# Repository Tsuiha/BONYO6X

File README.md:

# BONYO6X

　BONYO6Xは60%キーボードの汎用ケース、所謂Poker, GH60, DZ60等に対応したケースと互換性のあるPCBです。
 
　他人でも初見で使える, 自分でも不満なく使える, ことをコンセプトとしています。基本的なANSIは崩さずにカスタマイズ性も確保した構成を目指した、特化型でなく器用貧乏型のキーボードです。
 
　使用用途は実務からラフな普段使いまで, 一台で可もなく不可もなく, 満遍なくこなすことを想定しています。

　リポジトリに設計データが公開されています。 自由にしてください。

　[noteでも紹介しています](https://note.com/tsuiha/m/m13bdadaac60e)

## キー配置

　ANSIをベースに私の趣味を加え以下のようにカスタムしたものになります。

・2U Shift Layout  
　Row StaggeredよりもColumn StaggeredやOrtholinearが好きなこともあり、オフセット量の揃った2U Shiftの方が好みです。

・1.5U, 2U, 1.5U Thumb Cluster  
　2U スペースキーの左右に1.5U Modキーを配置し、レイヤー移動を前提とした配列としています。

・Arrow Keys  
　Arrow KeysがTop Layerにあると痒い時に手が届きます。DZ60系の詰めた配列ではなく、1.75U Shiftを端に、Arrow Keysはその内側に配置しています。

・Tactile Switch  
　キーボード右下にタクトスイッチを搭載可能です。マイクミュート, スクリーンショット, リプレイの保存 等、キースイッチと独立したFunctionキーとして使用できます。

画像はkeyboard-layout-editor.comにて作成しました。

## LED
　LEDが2個搭載可能です。デフォルトでは現在のレイヤーに対応して発光色が変化します。
　発光強度や色、光らせ方はファームウェアを改変し変更することができます。

## タクタイルスイッチ
　タクタイルスイッチが1個搭載可能です。ケース高に応じて高さのあったスイッチを使用してください。フローティングデザインのケースでは7mmのものを、通常デザインのケースでは11mmのものを画像では使用しています。

# 組み立て

## PCB & Switch Plate 
　誰かが製造したものを入手するか、公開されている設計データから自身で製造ください。JLCPCBを使用する際は発注データが公開されています。

## LED SK6812MINI-E x2
　オプションでLEDを取り付けることができます。

## Tactile Switch x1
　オプションでタクトスイッチを取り付けることができます。6x6mmサイズの2pinまたは4pinのものを使用することができます。

## qmk-vial
　ファームウェアにはqmk-vialを使用しています。

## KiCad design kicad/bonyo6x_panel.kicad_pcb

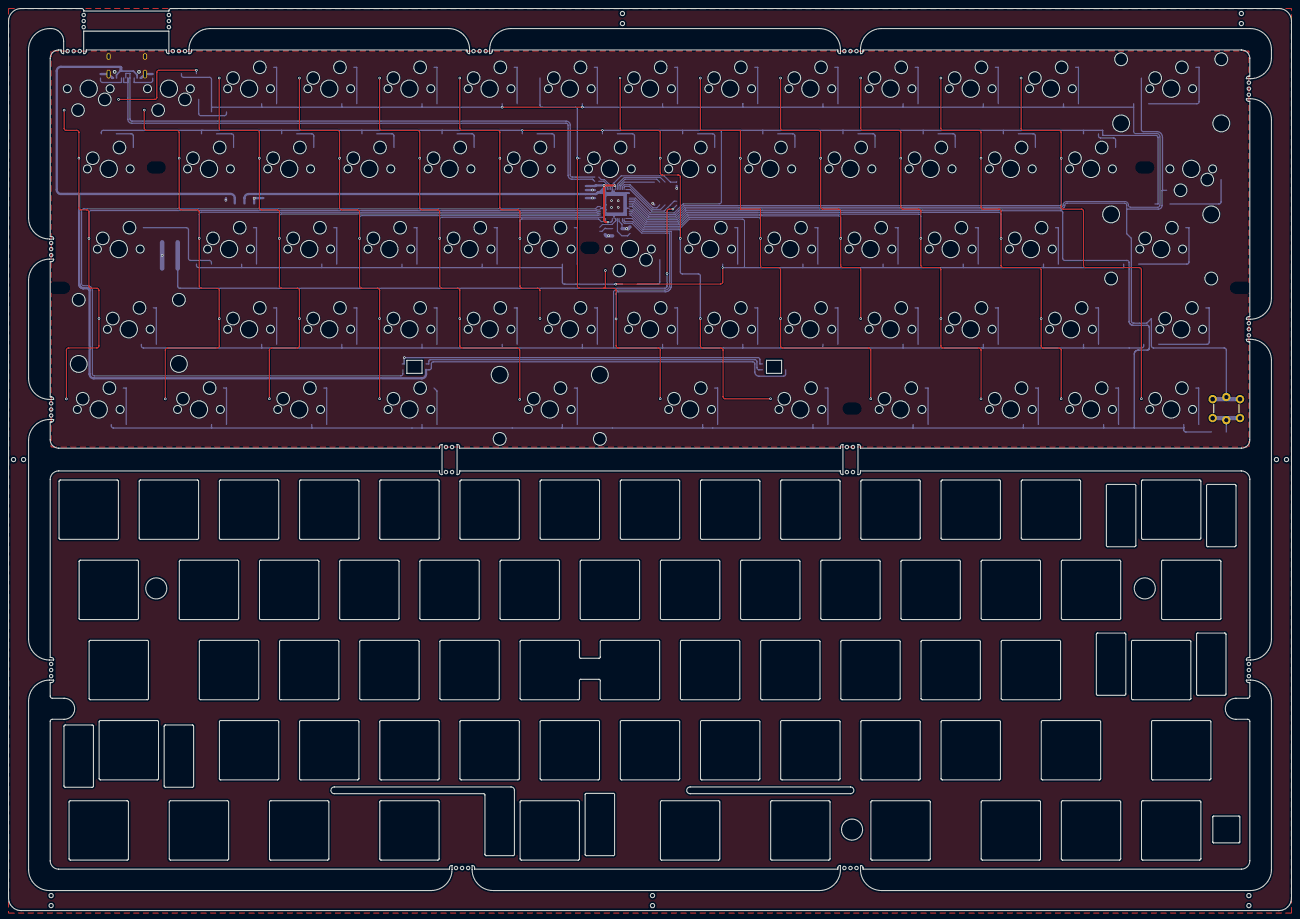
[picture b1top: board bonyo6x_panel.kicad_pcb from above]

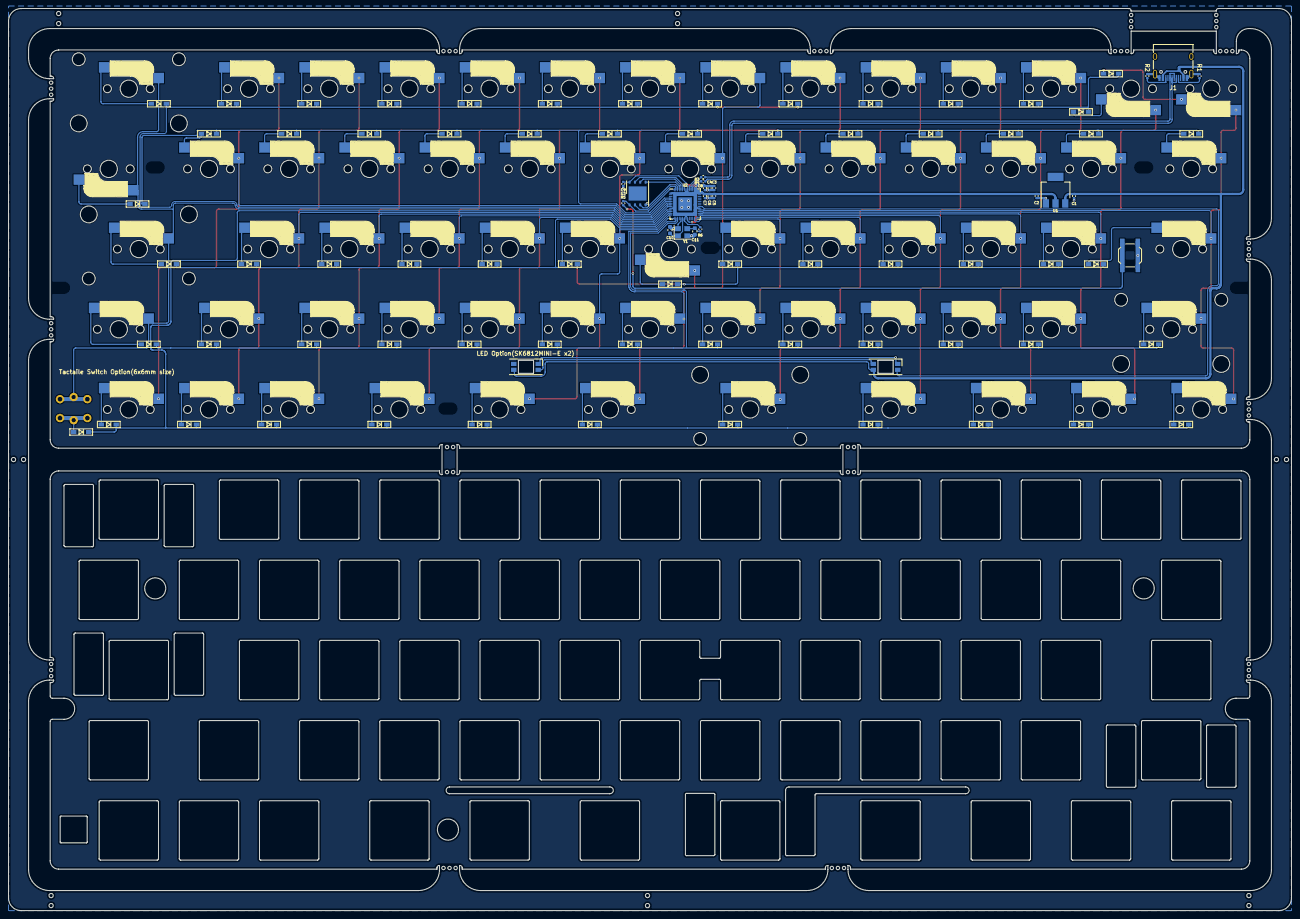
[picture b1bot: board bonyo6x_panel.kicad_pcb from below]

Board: 2 copper layers, 304.7 x 214.2 mm, 220 parts (25 on the bottom side), 107 nets.

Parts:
C1, C2: 10u; C_0402_1005Metric
C3, C4, C5, C6, C9: 100n; C_0402_1005Metric
C7, C8: 1u; C_0402_1005Metric
C10, C11: 30p; C_0603_1608Metric
D1, D2, D3, D4, D5, D6, D7, D8, D9, D10, D11, D12, D13, D14, D15, D16, D17, D18, D19, D20, D21, D22, D23, D24, D25, D26, D27, D28, D29, D30, D31, D32, D33, D34, D35, D36, D37, D38, D39, D40, D41, D42, D43, D44, D45, D46, D47, D48, D49, D50, D51, D52, D53, D54, D55, D56, D57, D58, D59, D60, D61, D62, D63, D64, D65, D66: D; Diode_SMD_noname
J1: USB_C_Receptacle; USB_C_Receptacle_HRO_TYPE-C-31-M-12
LED1, LED2: YS-SK6812MINI-E
R1, R2: 5.1k; C_0402_1005Metric
R3, R4: 27; C_0402_1005Metric
R5, R6: 1k; C_0402_1005Metric
SW1, SW2#2, SW3, SW4#2, SW5, SW6, SW7#2, SW8#2, SW9#2, SW10, SW11#2, SW12, SW13#2, SW16, SW17, SW18#2, SW19, SW20, SW21#2, SW22#2, SW23, SW24, SW25, SW26, SW27, SW30, SW31, SW32, SW33#2, SW34, SW35, SW36, SW37#2, SW38#2, SW39, SW40#2, SW43#2, SW44, SW45#2, SW46, SW47, SW48#2, SW49, SW50#2, SW51#2, SW52#2, SW53, SW63, SW64#2, SW65: SW_PUSH; CherryMX_Hotswap
SW1#2, SW2, SW3#2, SW4, SW5#2, SW6#2, SW7, SW8, SW9, SW10#2, SW11, SW12#2, SW13, SW16#2, SW17#2, SW18, SW19#2, SW20#2, SW21, SW22, SW23#2, SW24#2, SW25#2, SW26#2, SW27#2, SW30#2, SW31#2, SW32#2, SW33, SW36#2, SW37, SW38, SW39#2, SW40, SW43, SW44#2, SW45, SW46#2, SW47#2, SW48, SW49#2, SW50, SW51, SW52, SW53#2, SW63#2, SW64, SW65#2: SW_PUSH; SW_Hole_1u
SW14: SW_PUSH_2; SW_Hole_2u
SW14#2: SW_PUSH_2; CherryMX_Hotswap_2u
SW15, SW28, SW58#2, SW60, SW60#3: SW_PUSH_15; SW_Hole_1u
SW15#2, SW28#2, SW58, SW60#2: SW_PUSH_15; CherryMX_Hotswap_1.5u
SW29, SW54#2: SW_PUSH_175; CherryMX_Hotswap_1.75u
SW29#2, SW54: SW_PUSH_175; SW_Hole_1u
SW41: SW_PUSH_225; CherryMX_Hotswap_2u_r
SW41#2, SW42: SW_PUSH_225; SW_Hole_2u
SW42#2: SW_PUSH_225; CherryMX_Hotswap_2u
SW55, SW56#2, SW57, SW61, SW62#2: SW_PUSH_125; CherryMX_Hotswap_1.25u
SW55#2, SW56, SW57#2, SW61#2, SW62: SW_PUSH_125; SW_Hole_1u
SW59: SW_PUSH_2; CherryMX_Hotswap_2u_r
SW_boot1: SW_BOOT; SW_SPST_SKQG_WithStem
SW_tact1: SW_PUSH; tactileforkh60
U1: AMS1117-3.3; SOT-223
U2: RP2040; QFN-56-1EP_7x7mm_P0.4mm_EP3.2x3.2mm
U3: W25Q128JVS; WSON-8-1EP_6x5mm_P1.27mm_EP3.4x4.3mm
Y1: Crystal_GND24; Crystal_SMD_3225-4Pin_3.2x2.5mm

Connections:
+1V1: C3.1, C4.1, C8.1, U2.23 (DVDD), U2.45 (VREG_VOUT), U2.50 (DVDD)
+3V3: C2.1, C5.1, C6.1, C7.1, C9.1, U1.2 (VO), U2.1 (IOVDD), U2.10 (IOVDD), U2.22 (IOVDD), U2.33 (IOVDD), U2.42 (IOVDD), U2.43 (ADC_AVDD), U2.44 (VREG_IN), U2.48 (USB_VDD), U2.49 (IOVDD), U3.8 (VCC)
+5V: C1.1, J1.A4 (VBUS), J1.A9 (VBUS), J1.B4 (VBUS), J1.B9 (VBUS), LED1.1 (VDD), LED2.1 (VDD), U1.3 (VI)
/QSPI_SCLK: U2.52 (QSPI_SCLK), U3.6 (CLK)
/QSPI_SD0: U2.53 (QSPI_SD0), U3.5 (DI(IO0))
/QSPI_SD1: U2.55 (QSPI_SD1), U3.2 (DO(IO1))
/QSPI_SD2: U2.54 (QSPI_SD2), U3.3 (IO2)
/QSPI_SD3: U2.51 (QSPI_SD3), U3.7 (IO3)
/QSPI_SS: R5.1, U2.56 (QSPI_SS), U3.1 (~CS)
/USB_D+: J1.A6 (D+), J1.B6 (D+), R3.2
/USB_D-: J1.A7 (D-), J1.B7 (D-), R4.2
/XIN: C10.2, U2.20 (XIN), Y1.1
/XOUT: R6.1, U2.21 (XOUT)
/~USB_BOOT: R5.2, SW_boot1.1
GND: C1.2, C2.2, C3.2, C4.2, C5.2, C6.2, C7.2, C8.2, C9.2, C10.1, C11.2, J1.A1 (GND), J1.A12 (GND), J1.B1 (GND), J1.B12 (GND), J1.S1 (SHIELD), LED1.3 (VSS), LED2.3 (VSS), R1.1, R2.1, SW_boot1.2, U1.1 (GND), U2.19 (TESTEN), U2.57 (GND), U3.4 (GND), Y1.2, Y1.4
LED: LED1.4 (DIN), U2.34 (GPIO22)
unnamed: C11.1, R6.2, Y1.3
unnamed: D1.2 (A), SW1.1
unnamed: D2.2 (A), SW2#2.1
unnamed: D3.2 (A), SW3.2
unnamed: D4.2 (A), SW4#2.2
unnamed: D5.2 (A), SW5.2
unnamed: D6.2 (A), SW6.2
unnamed: D7.2 (A), SW7#2.2
unnamed: D8.2 (A), SW8#2.2
unnamed: D9.2 (A), SW9#2.2
unnamed: D10.2 (A), SW10.2
unnamed: D11.2 (A), SW11#2.2
unnamed: D12.2 (A), SW12.2
unnamed: D13.2 (A), SW13#2.2
unnamed: D14.2 (A), SW14#2.2
unnamed: D15.2 (A), SW15#2.2
unnamed: D16.2 (A), SW16.2
unnamed: D17.2 (A), SW17.2
unnamed: D18.2 (A), SW18#2.2
unnamed: D19.2 (A), SW19.2
unnamed: D20.2 (A), SW20.2
unnamed: D21.2 (A), SW21#2.2
unnamed: D22.2 (A), SW22#2.2
unnamed: D23.2 (A), SW23.2
unnamed: D24.2 (A), SW24.2
unnamed: D25.2 (A), SW25.2
unnamed: D26.2 (A), SW26.2
unnamed: D27.2 (A), SW27.2
unnamed: D28.2 (A), SW28#2.1
unnamed: D29.2 (A), SW29.2
unnamed: D30.2 (A), SW30.2
unnamed: D31.2 (A), SW31.2
unnamed: D32.2 (A), SW32.2
unnamed: D33.2 (A), SW33#2.2
unnamed: D34.2 (A), SW34.2
unnamed: D35.2 (A), SW35.1
unnamed: D36.2 (A), SW36.2
unnamed: D37.2 (A), SW37#2.2
unnamed: D38.2 (A), SW38#2.2
unnamed: D39.2 (A), SW39.2
unnamed: D40.2 (A), SW40#2.2
unnamed: D41.2 (A), SW41.2
unnamed: D42.2 (A), SW42#2.2
unnamed: D43.2 (A), SW43#2.2
unnamed: D44.2 (A), SW44.2
unnamed: D45.2 (A), SW45#2.2
unnamed: D46.2 (A), SW46.2
unnamed: D47.2 (A), SW47.2
unnamed: D48.2 (A), SW48#2.2
unnamed: D49.2 (A), SW49.2
unnamed: D50.2 (A), SW50#2.2
unnamed: D51.2 (A), SW51#2.2
unnamed: D52.2 (A), SW52#2.2
unnamed: D53.2 (A), SW53.2
unnamed: D54.2 (A), SW54#2.2
unnamed: D55.2 (A), SW55.2
unnamed: D56.2 (A), SW56#2.2
unnamed: D57.2 (A), SW57.2
unnamed: D58.2 (A), SW58.2
unnamed: D59.2 (A), SW59.2
unnamed: D60.2 (A), SW60#2.2
unnamed: D61.2 (A), SW61.2
unnamed: D62.2 (A), SW62#2.2
unnamed: D63.2 (A), SW63.2
unnamed: D64.2 (A), SW64#2.2
unnamed: D65.2 (A), SW65.2
unnamed: D66.2 (A), SW_tact1.2
unnamed: J1.A5 (CC1), R1.2
unnamed: J1.B5 (CC2), R2.2
unnamed: LED1.2 (DOUT), LED2.4 (DIN)
unnamed: R4.1, U2.46 (USB_DM)
unnamed: R3.1, U2.47 (USB_DP)
c0: SW1.2, SW15#2.1, SW29.1, SW42#2.1, SW55.1, U2.32 (GPIO21)
c1: SW2#2.2, SW16.1, SW30.1, SW43#2.1, SW56#2.1, U2.31 (GPIO20)
c2: SW3.1, SW17.1, SW31.1, SW44.1, SW57.1, U2.30 (GPIO19)
c3: SW4#2.1, SW18#2.1, SW32.1, SW45#2.1, SW58.1, U2.29 (GPIO18)
c4: SW5.1, SW19.1, SW33#2.1, SW46.1, SW59.1, U2.28 (GPIO17)
c5: SW6.1, SW20.1, SW34.1, SW47.1, U2.27 (GPIO16)
c6: SW7#2.1, SW21#2.1, SW35.2, SW48#2.1, SW60#2.1, U2.16 (GPIO13)
c7: SW8#2.1, SW22#2.1, SW36.1, SW49.1, SW61.1, U2.15 (GPIO12)
c8: SW9#2.1, SW23.1, SW37#2.1, SW50#2.1, SW62#2.1, U2.13 (GPIO10)
c9: SW10.1, SW24.1, SW38#2.1, SW51#2.1, U2.12 (GPIO9)
c10: SW11#2.1, SW25.1, SW39.1, SW52#2.1, SW63.1, U2.11 (GPIO8)
c11: SW12.1, SW26.1, SW40#2.1, SW53.1, SW64#2.1, U2.9 (GPIO7)
c12: SW13#2.1, SW27.1, SW65.1, U2.5 (GPIO3)
c13: SW14#2.1, SW28#2.2, SW41.1, SW54#2.1, SW_tact1.1, U2.7 (GPIO5)
r0: D1.1 (K), D2.1 (K), D3.1 (K), D4.1 (K), D5.1 (K), D6.1 (K), D7.1 (K), D8.1 (K), D9.1 (K), D10.1 (K), D11.1 (K), D12.1 (K), D13.1 (K), D14.1 (K), U2.6 (GPIO4)
r1: D15.1 (K), D16.1 (K), D17.1 (K), D18.1 (K), D19.1 (K), D20.1 (K), D21.1 (K), D22.1 (K), D23.1 (K), D24.1 (K), D25.1 (K), D26.1 (K), D27.1 (K), D28.1 (K), U2.4 (GPIO2)
r2: D29.1 (K), D30.1 (K), D31.1 (K), D32.1 (K), D33.1 (K), D34.1 (K), D35.1 (K), D36.1 (K), D37.1 (K), D38.1 (K), D39.1 (K), D40.1 (K), D41.1 (K), U2.14 (GPIO11)
r3: D42.1 (K), D43.1 (K), D44.1 (K), D45.1 (K), D46.1 (K), D47.1 (K), D48.1 (K), D49.1 (K), D50.1 (K), D51.1 (K), D52.1 (K), D53.1 (K), D54.1 (K), U2.17 (GPIO14)
r4: D55.1 (K), D56.1 (K), D57.1 (K), D58.1 (K), D59.1 (K), D60.1 (K), D61.1 (K), D62.1 (K), D63.1 (K), D64.1 (K), D65.1 (K), D66.1 (K), U2.8 (GPIO6)

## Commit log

2025-03-03 Create LICENSE
